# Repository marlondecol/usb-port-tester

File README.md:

Design of a little USB port tester device, similar to a flash drive, designed with KiCad.

_Project under development_.

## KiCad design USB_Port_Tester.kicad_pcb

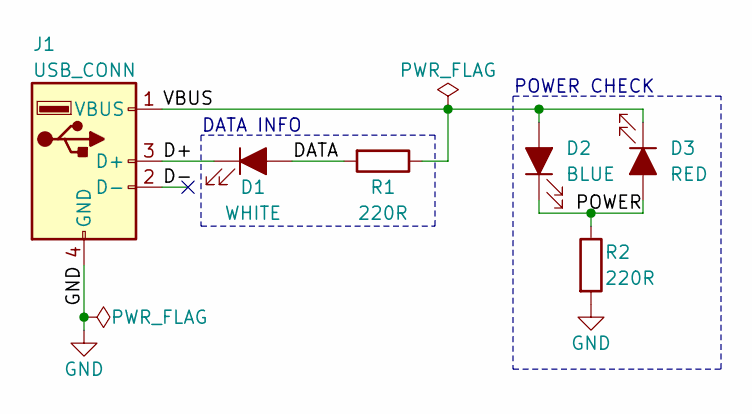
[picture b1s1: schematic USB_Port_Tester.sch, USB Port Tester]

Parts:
D1: WHITE; LED_0805_2012Metric
D2: BLUE; LED_0805_2012Metric
D3: RED; LED_0805_2012Metric
J1: USB_CONN; USB_A_On_Trace
R1, R2: 220R; R_0805_2012Metric

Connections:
/D+: D1.1 (K), J1.3 (D+)
/D-: J1.2 (D-)
/DATA: D1.2 (A), R1.2
/POWER: D2.1 (K), D3.2 (A), R2.1
/VBUS: D2.2 (A), D3.1 (K), J1.1 (VBUS), R1.1
GND: J1.4 (GND), R2.2

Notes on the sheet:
POWER CHECK
DATA INFO

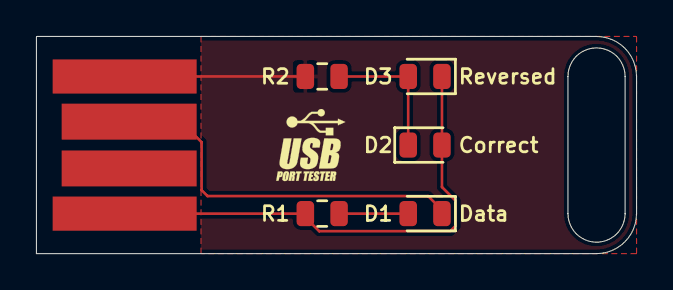
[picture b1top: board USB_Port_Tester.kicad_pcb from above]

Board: 2 copper layers, 33.3 x 12.1 mm, 6 parts (0 on the bottom side), 5 nets.

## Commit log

2020-01-20 License assigned
2020-01-20 .gitignore file added
2020-01-20 First revision finished
2020-01-21 License corrected in page settings

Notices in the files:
USB_Port_Tester.kicad_pcb:
CERN Open Hardware Licence v1.2
